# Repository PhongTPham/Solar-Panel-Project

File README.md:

# Introduction
This Solar Panel Project is a class project for a Power Electronics class. The aim was to build a device related to power that can be used for personal use, is relatively inexpensive and simple to assemble.

## [Link to the hardware](https://github.com/PhongTPham/Solar-Panel-Project/wiki/Main-Page#hardware)

This is what the completed circuit looks like:

## [Link to the Testing](https://github.com/PhongTPham/Solar-Panel-Project/wiki/Main-Page#testing)

# Current Status of this project:
At the moment this project doesn't quite work. When I was soldering parts onto the PCB something happened that fried my buck booster IC and as a result the entire section after the SPDT switch is rendered unusable since it feeds directly to the buck booster. If I connect my battery straight to the USB port and plug in a charger than it works just fine, but that defeats the purpose of the project.

## [Link to Future Considerations](https://github.com/PhongTPham/Solar-Panel-Project/wiki/Main-Page#future-considerations)

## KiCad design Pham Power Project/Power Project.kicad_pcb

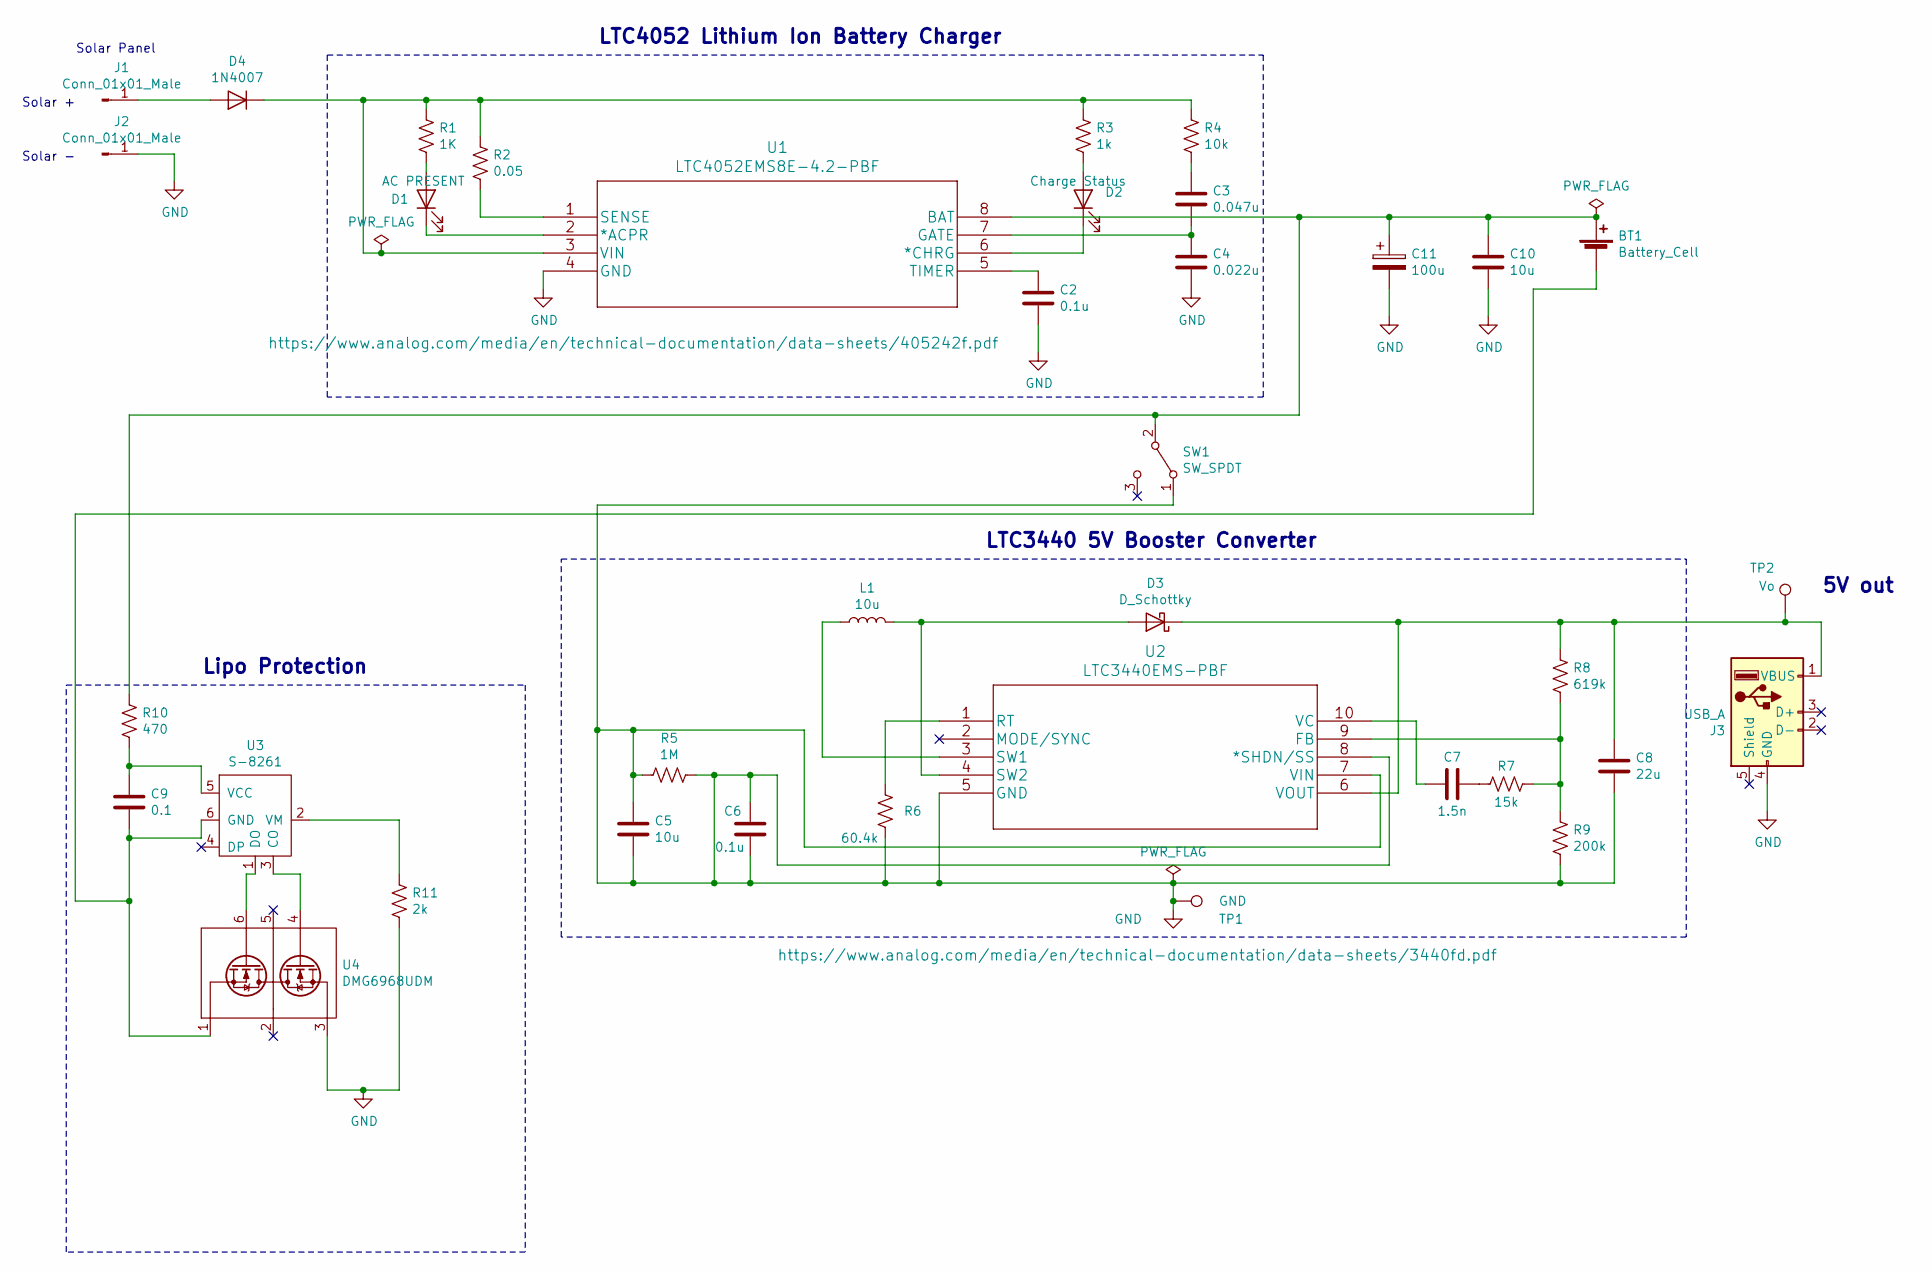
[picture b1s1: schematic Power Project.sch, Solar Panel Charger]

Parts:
BT1: Battery_Cell; BatteryHolder_MPD_BH-18650-PC2
C2, C6: 0.1u; C_0805_2012Metric
C3: 0.047u; C_0805_2012Metric
C4: 0.022u; C_0805_2012Metric
C5, C10: 10u; C_0805_2012Metric
C7: 1.5n; C_0805_2012Metric
C8: 22u; C_0805_2012Metric
C9: 0.1; C_0805_2012Metric
C11: 100u; CP_Elec_6.3x5.4_Nichicon
D1: AC PRESENT; LED_0805_2012Metric
D2: Charge Status; LED_0805_2012Metric
D3: D_Schottky; D_SMC
D4: 1N4007; D_DO-41_SOD81_P10.16mm_Horizontal
J1, J2: Conn_01x01_Male; SolderWirePad_1x01_Drill0.8mm
J3: USB_A; USB_A_CNCTech_1001-011-01101_Horizontal
L1: 10u; L_0805_2012Metric
R1: 1K; R_0805_2012Metric
R2: 0.05; R_0805_2012Metric
R3: 1k; R_0805_2012Metric
R4: 10k; R_0805_2012Metric
R5: 1M; R_0805_2012Metric
R6: 60.4k; R_0805_2012Metric
R7: 15k; R_0805_2012Metric
R8: 619k; R_0805_2012Metric
R9: 200k; R_0805_2012Metric
R10: 470; R_0805_2012Metric
R11: 2k; R_0805_2012Metric
SW1: SW_SPDT; SW_SPDT_PCM12
TP1: GND; TestPoint_Plated_Hole_D2.0mm
TP2: Vo; TestPoint_Plated_Hole_D2.0mm
U1: LTC4052EMS8E-4.2-PBF
U2: LTC3440EMS-PBF
U3: S-8261; SOT-23-6
U4: DMG6968UDM; SOT-23-6

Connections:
GND: C2.2, C4.2, C5.1, C5.2, C6.1, C6.2, C8.2, C10.2, C11.2, J2.1, J3.4 (GND), R5.1, R5.2, R6.2, R9.2, R11.2, SW1.1 (A), TP1.1, U1.4 (GND), U2.5 (GND), U2.7 (VIN), U2.8 (*SHDN/SS), U4.3
unnamed: BT1.1 (+), C10.1, C11.1, R10.1, SW1.2 (B), U1.8 (BAT)
unnamed: BT1.2 (-), C9.2, U3.6 (GND), U4.1
unnamed: C2.1, U1.5 (TIMER)
unnamed: C3.1, R4.2
unnamed: C3.2, C4.1, U1.7 (GATE)
unnamed: C7.1, R7.2
unnamed: C7.2, U2.10 (VC)
unnamed: C8.1, D3.1 (K), J3.1 (VBUS), R8.1, TP2.1, U2.6 (VOUT)
unnamed: C9.1, R10.2, U3.5 (VCC)
unnamed: D1.1 (K), U1.2 (*ACPR)
unnamed: D1.2 (A), R1.2
unnamed: D2.1 (K), U1.6 (*CHRG)
unnamed: D2.2 (A), R3.2
unnamed: D3.2 (A), L1.2, U2.4 (SW2)
unnamed: D4.1 (K), R1.1, R2.1, R3.1, R4.1, U1.3 (VIN)
unnamed: D4.2 (A), J1.1
unnamed: L1.1, U2.3 (SW1)
unnamed: R2.2, U1.1 (SENSE)
unnamed: R6.1, U2.1 (RT)
unnamed: R7.1, R8.2, R9.1, U2.9 (FB)
unnamed: R11.1, U3.2 (VM)
unnamed: U3.1 (DO), U4.6
unnamed: U3.3 (CO), U4.4

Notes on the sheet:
Solar Panel
Solar +
Solar -
5V out
LTC4052 Lithium Ion Battery Charger
Lipo Protection
LTC3440 5V Booster Converter

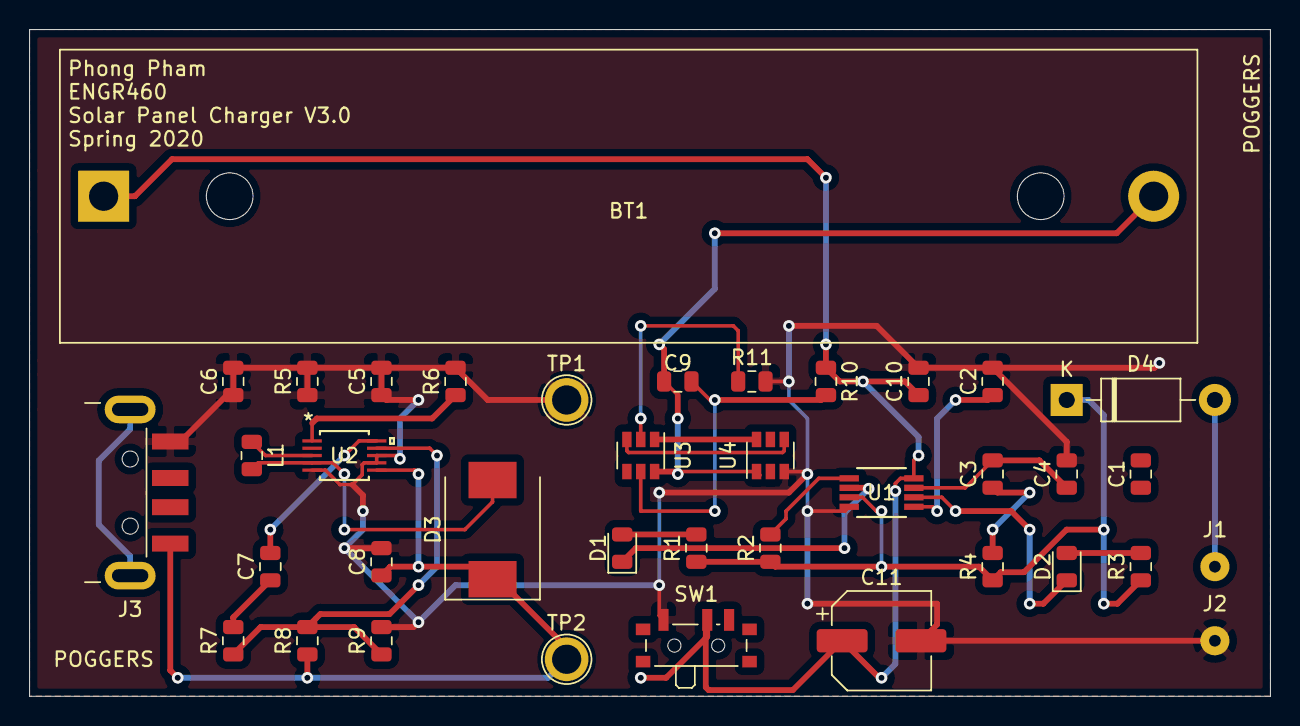
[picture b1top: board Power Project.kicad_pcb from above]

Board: 2 copper layers, 85.1 x 45.7 mm, 38 parts (0 on the bottom side), 24 nets.

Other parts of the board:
C1: 1uF; C_0805_2012Metric

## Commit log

2020-06-03 Added KICAD files for Solar Panel Project
2020-06-03 Added testing procedure for Solar Panel Project
2020-06-03 Added App notes for the solar panel project
2020-06-11 BOM for the initial PCB design
2020-06-11 Kicad Libraries
    added libraries for kicad parts

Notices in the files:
parts and their libraries:
Copyright 2016 Accelerated Designs. All rights reserved.
